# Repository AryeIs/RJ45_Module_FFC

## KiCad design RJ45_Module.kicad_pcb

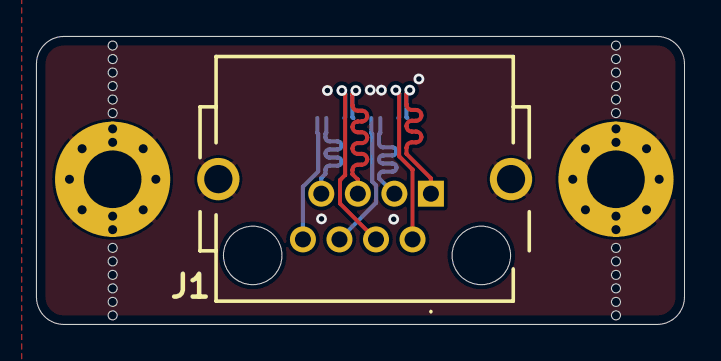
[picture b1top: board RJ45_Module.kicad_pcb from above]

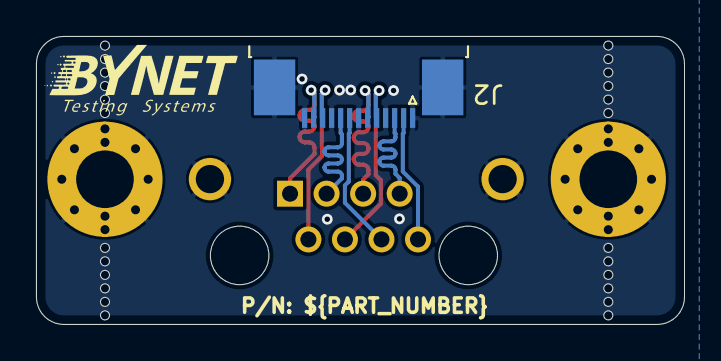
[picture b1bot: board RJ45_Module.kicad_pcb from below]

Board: 4 copper layers, 36.0 x 16.0 mm, 6 parts (2 on the bottom side), 9 nets.

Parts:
 : LOGO; BYNET_LOGO_4000x4000
 #2: LOGO; BYNET_LOGO_4000x4000
J1: RJHSE3380A1
J2: Conn_01x13_MountingPin; TE_1-1734839-3_1x13-1MP_P0.5mm_Horizontal
MH1, MH2: MountingHole_Pad; MountingHole_3.2mm_M3_Pad_Via

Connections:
/ETH1_1N: J1.2, J2.11
/ETH1_1P: J1.1, J2.12
/ETH1_2N: J1.6, J2.8
/ETH1_2P: J1.3, J2.9
/ETH1_3N: J1.5, J2.6
/ETH1_3P: J1.4, J2.5
/ETH1_4N: J1.8, J2.2
/ETH1_4P: J1.7, J2.3
GNDPWR: J1.SH, J2.1, J2.4, J2.7, J2.10, J2.13, J2.MP (MountPin), MH1.1, MH2.1

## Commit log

2024-01-11 Initial commit: Rev 1.0
2024-01-11 Initial commit: Rev 1.1
2024-01-11 Mouser bites to mounting holes added
